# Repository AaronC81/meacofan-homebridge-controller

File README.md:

# Meacofan HomeBridge Controller

This project connects a [MeacoFan 1056](https://www.meaco.com/products/meacofan-1056-air-circulator)
desk fan to HomeKit using [Homebridge](https://homebridge.io/), enabling it to be controlled using
your iOS device or Siri.

The PCB blasts the same IR commands as the fan's real remote control, accepting commands over I2C so
that it can be controlled from a Raspberry Pi.

> [!WARNING]
> This is quite rough around the edges. I wouldn't recommend building one of these yourself!

## PCB

The PCB is a KiCad project in `hardware/pcb`. (The BOM is hopefully self-explanatory from the
schematic!)

Once assembled, the on-board ISP port can be used to flash the ATtiny85. You'll also need to set
appropriate fuses to use the internal 8 MHz clock, which the software relies on. The AVRDUDE flags
for this are:

```
-U lfuse:w:0xe2:m -U hfuse:w:0xdf:m -U efuse:w:0xff:m
```

(Note that, until the clock is increased with these fuses, you may need to slow down ISP
communication speed: `-B 125kHz`)

## Homebridge Plugin

`homebridge-plugin` contains a Homebridge accessory plugin which implements the
[`Fan`](https://developers.homebridge.io/#/service/Fan) service. This sends I2C commands to the PCB
to match the desired speed set through HomeKit. (HomeKit only supports 0%-100% speeds, so these
are mapped onto the fan's 1-12 speed settings.)

You will need the `i2c-tools` package installed to provide the `i2ctransfer` command-line tool.
Make sure that I2C is enabled in your `raspi-config` too. If everything is working OK, the device
should appear at address 0x40 in `i2cdetect`.

## Software

The software is written as a PlatformIO project targeting the ATtiny85, using the Arduino framework.

### Communication

The ATtiny85 acts as a bit-banged I2C peripheral on address 0x40. Only one operation is supported,
a single-byte write where the byte is in the following format:

```
  .--------------- checksum - number of 1s in rest of packet
.-'-.
c c c 1 s s s s
        '--.--'
           '------ new desired speed (0-12), 0 means off
```

These packets are designed to be idempotent, so your host should probably send these multiple times
to account for the sloppy I2C bit-banging.

### IR Commands

The fan operates with NEC-format IR codes at address 0x80. The individual commands are documented
below: 

| Purpose                | Command | Raw        |
| ---------------------- | ------- | ---------- |
| Power                  | 0x92    | 0x6D927F80 |
| Vertical oscillation   | 0x8A    | 0x758A7F80 |
| Horizontal oscillation | 0x87    | 0x78877F80 |
| Eco                    | 0x81    | 0x7E817F80 |
| Pre-on                 | 0x82    | 0x7D827F80 |
| Pre-off                | 0x83    | 0x7C837F80 |
| Light                  | 0x9E    | 0x619E7F80 |
| Speed up               | 0x89    | 0x76897F80 |
| Speed down             | 0x9F    | 0x609F7F80 |

## Enclosure

There's a very rough 3D printed enclosure which keeps the IR LED aimed in `hardware/case`.

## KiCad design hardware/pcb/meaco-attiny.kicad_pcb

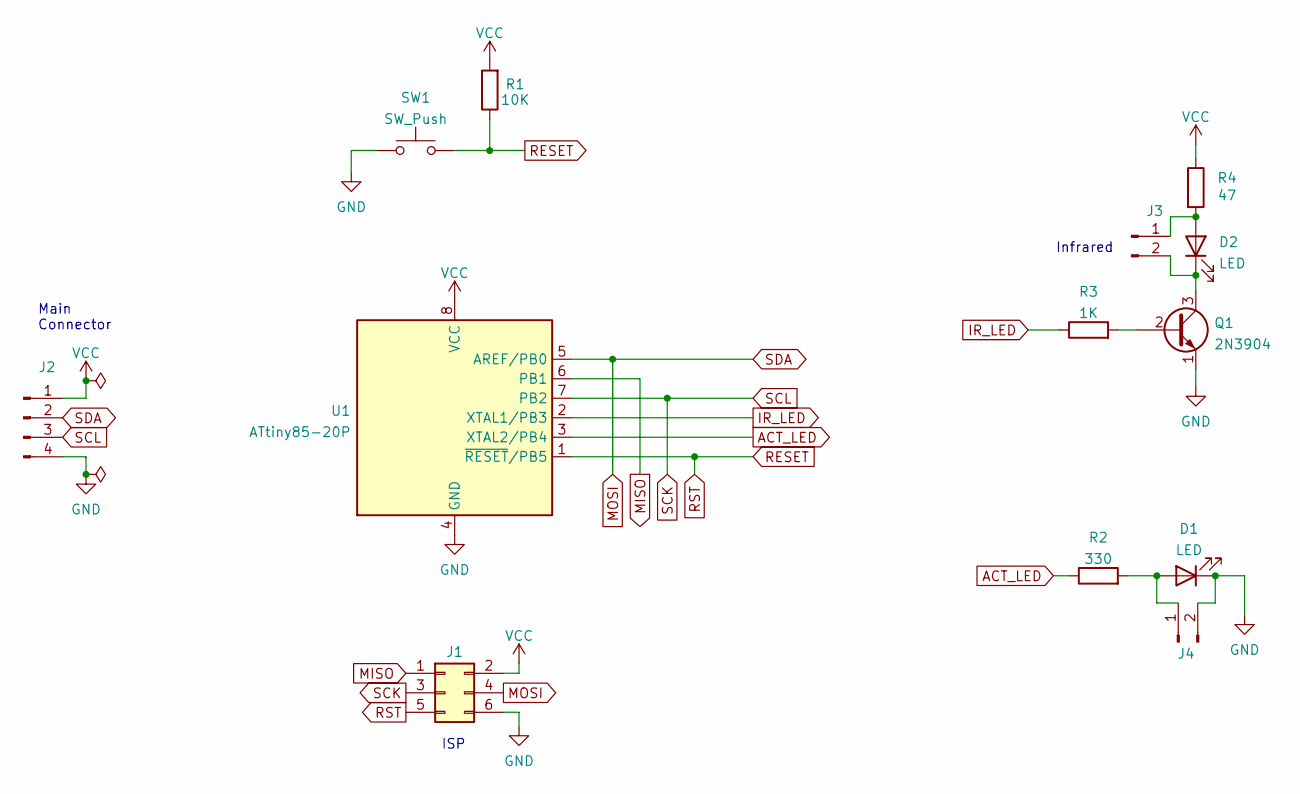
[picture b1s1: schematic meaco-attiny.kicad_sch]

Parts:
D1, D2: LED; LED_D5.0mm
J1: Conn_02x03_Odd_Even; PinHeader_2x03_P2.54mm_Vertical
J2: Conn_01x04_Male; PinHeader_1x04_P2.54mm_Vertical
J3, J4: Conn_01x02_Male; PinHeader_1x02_P2.54mm_Vertical
Q1: 2N3904; TO-92_Inline
R1: 10K; R_0603_1608Metric
R2: 330; R_0603_1608Metric
R3: 1K; R_0603_1608Metric
R4: 47; R_0603_1608Metric
SW1: SW_Push; SW_PUSH_6mm
U1: ATtiny85-20P; DIP-8_W7.62mm

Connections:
ACT_LED: R2.1, U1.3 (XTAL2/PB4)
GND: D1.1 (K), J1.6, J2.4, J4.2, Q1.1 (E), SW1.1, U1.4 (GND)
IR_LED: R3.1, U1.2 (XTAL1/PB3)
MISO: J1.1, U1.6 (PB1)
MOSI: J1.4, J2.2, U1.5 (AREF/PB0)
unnamed: D1.2 (A), J4.1, R2.2
unnamed: D2.1 (K), J3.2, Q1.3 (C)
unnamed: D2.2 (A), J3.1, R4.2
unnamed: Q1.2 (B), R3.2
RESET: J1.5, R1.1, SW1.2, U1.1 (~RESET/PB5)
SCK: J1.3, J2.3, U1.7 (PB2)
VCC: J1.2, J2.1, R1.2, R4.1, U1.8 (VCC)

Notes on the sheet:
Infrared
ISP
Main Connector

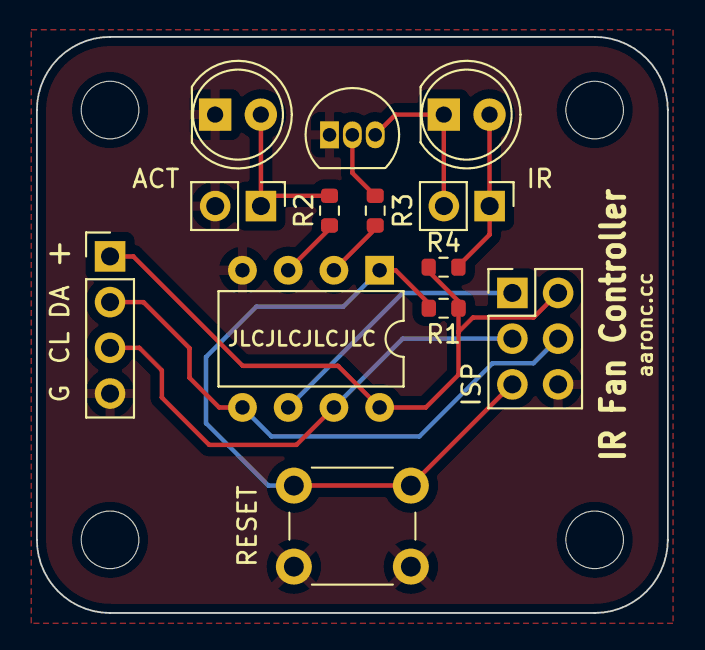
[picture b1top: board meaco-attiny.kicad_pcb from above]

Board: 2 copper layers, 35.1 x 32.0 mm, 13 parts (0 on the bottom side), 12 nets.

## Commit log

2024-02-18 Initial commit
    ATtiny85 blinky, no external oscillator
2024-02-18 Run at 8MHz
2024-02-19 Add IRsend which doesn't work
    I think it's a clock issue
2024-02-19 It works! Manually write NEC IR send code
2024-02-21 Add Python class to talk to FT260 for PC<->I2C testing
2024-02-21 Change IR pin
2024-02-21 Refactor IR into a separate namespace
2024-02-21 Ignore some stuff
2024-02-21 Terrible I2C bitbang
2024-02-21 Filter on address
2024-02-21 Add a dedicated I2C activity LED pin
2024-02-21 Drop in a new digitalWrite/ReadFast library
2024-02-21 Re-enable IR transmission - it works!
2024-02-21 Add fan model with packet control
2024-02-22 Add higher-level Python wrapper
2024-02-22 Break out I2C handling into a module
2024-02-22 Tidy up I2C code a little bit
2024-02-22 Add a crap timer to bail out of broken transmission
    This does actually work; interrupt-based hardware timers would be way
    better, but this was much easier to implement :P
2024-02-25 Blink on power on
2024-02-25 Handle sleep mode
2024-02-25 Add checksum system to avoid incorrect I2C peripheral message data
    In combination with having the Node app send the packet several times,
    this leads to a vaguely reliable tranmission, I think....?
2024-02-26 Pad out delay a bit
2024-02-26 Add basic Homebridge plugin for power toggling
    Based on: https://github.com/homebridge/homebridge-examples/tree/latest/accessory-example-typescript
2024-02-26 Working speed control from Homebridge plugin
2024-02-27 Add WIP PCB
2024-02-27 Put swirly pattern on back of PCB
2024-02-27 JLC! JLC! JLC! JLC!
2024-03-13 Add basic case
2024-03-13 Add LICENSE and README
